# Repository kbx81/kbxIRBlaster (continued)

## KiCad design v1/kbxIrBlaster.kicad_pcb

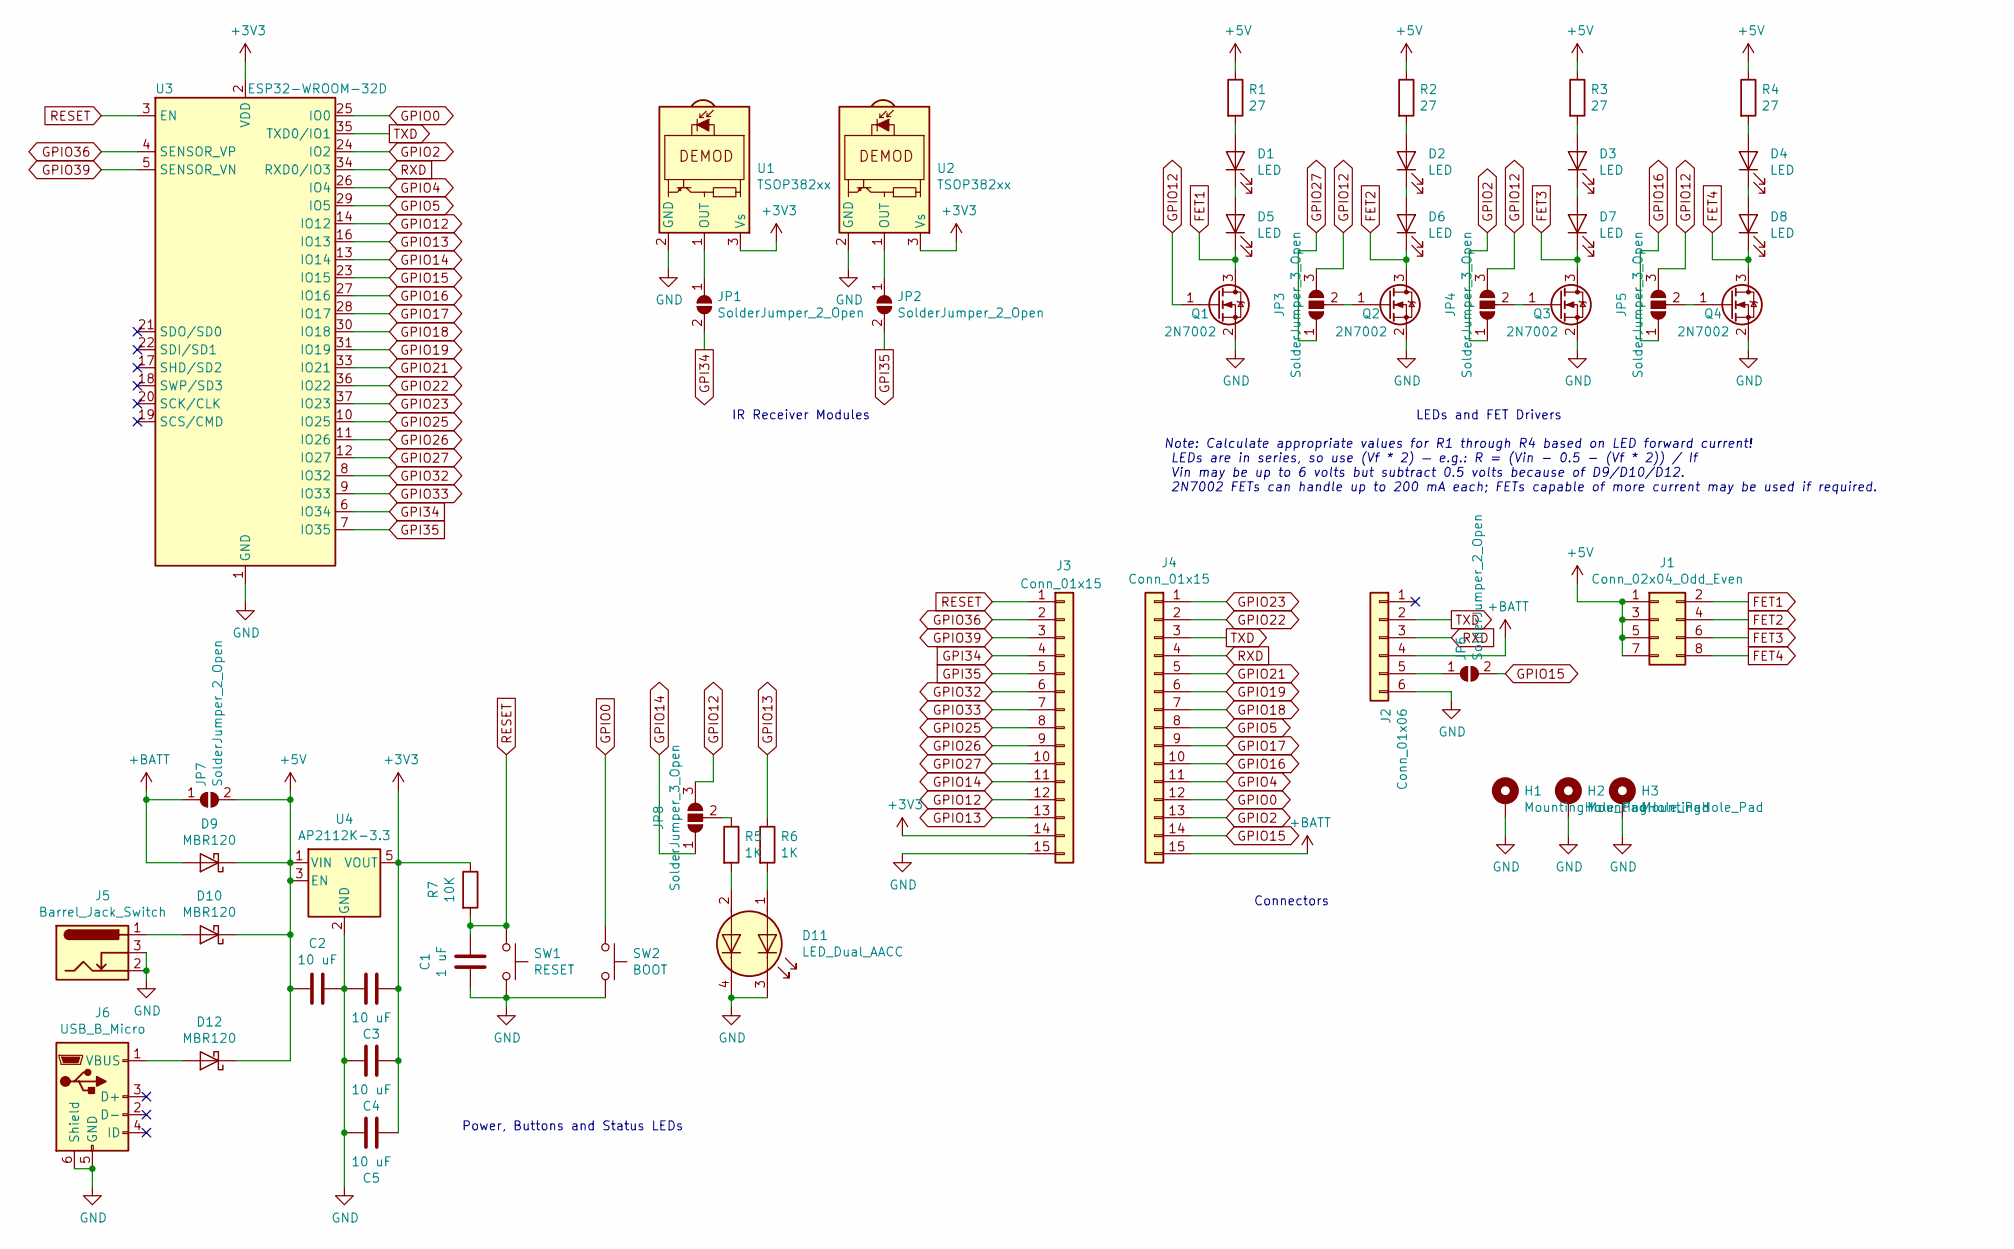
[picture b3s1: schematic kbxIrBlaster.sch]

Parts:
C1: 1 uF; C_0805_2012Metric_Pad1.15x1.40mm_HandSolder; MPN1 C0805C105K4RACTU
C2, C3, C4, C5: 10 uF; C_0805_2012Metric_Pad1.15x1.40mm_HandSolder; MPN1 GRM21BC81C106ME15L
D1, D2, D3, D4, D5, D6, D7, D8: LED; LED_D5.0mm; MPN1 LTE-4206
D9, D10, D12: MBR120; D_SOD-123F; MPN1 MBR120VLSFT1G
D11: LED_Dual_AACC; LED_Cree-PLCC4_3.2x2.8mm_CCW; MPN1 APB3025ESGC-F01
H1, H2, H3: MountingHole_Pad; MountingHole_2.5mm_Pad_Via
J1: Conn_02x04_Odd_Even; PinHeader_2x04_P2.54mm_Vertical
J2: Conn_01x06; PinHeader_1x06_P2.54mm_Vertical
J3, J4: Conn_01x15; PinHeader_1x15_P2.54mm_Vertical
J5: Barrel_Jack_Switch; BarrelJack_Horizontal; MPN1 163-179PH-EX
J6: USB_B_Micro; USB_Micro-B_Molex-105017-0001; MPN1 105017-0001
JP1, JP2, JP6, JP7: SolderJumper_2_Open; SolderJumper-2_P1.3mm_Open_RoundedPad1.0x1.5mm
JP3, JP4, JP5, JP8: SolderJumper_3_Open; SolderJumper-3_P1.3mm_Open_RoundedPad1.0x1.5mm
Q1, Q2, Q3, Q4: 2N7002; SOT-23; MPN1 2N7002-7-F
R1, R2, R3, R4: 27; R_0805_2012Metric_Pad1.15x1.40mm_HandSolder; MPN1 RC0805FR-0727RL
R5, R6: 1K; R_0805_2012Metric_Pad1.15x1.40mm_HandSolder; MPN1 RC0805FR-071KL
R7: 10K; R_0805_2012Metric_Pad1.15x1.40mm_HandSolder; MPN1 RC0805FR-0710KL
SW1: RESET; SW_Push_1P1T_NO_CK_KMR2; MPN1 KMR221GLFS
SW2: BOOT; SW_Push_1P1T_NO_CK_KMR2; MPN1 KMR221GLFS
U1: TSOP382xx; Vishay_MINICAST-3Pin; MPN1 TSOP38238
U2: TSOP382xx; Vishay_MINICAST-3Pin; MPN1 TSOP38256
U3: ESP32-WROOM-32D; ESP32-WROOM-32; MPN1 ESP32-WROOM-32D
U4: AP2112K-3.3; SOT-23-5; MPN1 AP2112K-3.3TRG1

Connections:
+3V3: C3.2, C4.2, C5.2, J3.14, R7.1, U1.3 (Vs), U2.3 (Vs), U3.2 (VDD), U4.5 (VOUT)
+5V: C2.2, D9.1 (K), D10.1 (K), D12.1 (K), J1.1, J1.3, J1.5, J1.7, JP7.2 (B), R1.1, R2.1, R3.1, R4.1, U4.1 (VIN), U4.3 (EN)
+BATT: D9.2 (A), J2.4, J4.15, JP7.1 (A)
FET1: D5.1 (K), J1.2, Q1.3 (D)
FET2: D6.1 (K), J1.4, Q2.3 (D)
FET3: D7.1 (K), J1.6, Q3.3 (D)
FET4: D8.1 (K), J1.8, Q4.3 (D)
GND: C1.2, C2.1, C3.1, C4.1, C5.1, D11.3 (K1), D11.4 (K2), H1.1, H2.1, H3.1, J2.6, J3.15, J5.2, J5.3, J6.5 (GND), J6.6 (Shield), Q1.2 (S), Q2.2 (S), Q3.2 (S), Q4.2 (S), SW1.2, SW2.2, U1.2 (GND), U2.2 (GND), U3.1 (GND), U3.15 (GND), U3.38 (GND), U3.39 (GND), U4.2 (GND)
GPI34: J3.4, JP1.2 (B), U3.6 (IO34)
GPI35: J3.5, JP2.2 (B), U3.7 (IO35)
GPIO0: J4.12, SW2.1, U3.25 (IO0)
GPIO2: J4.13, JP4.1 (A), U3.24 (IO2)
GPIO4: J4.11, U3.26 (IO4)
GPIO5: J4.8, U3.29 (IO5)
GPIO12: J3.12, JP3.3 (B), JP4.3 (B), JP5.3 (B), JP8.3 (B), Q1.1 (G), U3.14 (IO12)
GPIO13: J3.13, R6.1, U3.16 (IO13)
GPIO14: J3.11, JP8.1 (A), U3.13 (IO14)
GPIO15: J4.14, JP6.2 (B), U3.23 (IO15)
GPIO16: J4.10, JP5.1 (A), U3.27 (IO16)
GPIO17: J4.9, U3.28 (IO17)
GPIO18: J4.7, U3.30 (IO18)
GPIO19: J4.6, U3.31 (IO19)
GPIO21: J4.5, U3.33 (IO21)
GPIO22: J4.2, U3.36 (IO22)
GPIO23: J4.1, U3.37 (IO23)
GPIO25: J3.8, U3.10 (IO25)
GPIO26: J3.9, U3.11 (IO26)
GPIO27: J3.10, JP3.1 (A), U3.12 (IO27)
GPIO32: J3.6, U3.8 (IO32)
GPIO33: J3.7, U3.9 (IO33)
GPIO36: J3.2, U3.4 (SENSOR_VP)
GPIO39: J3.3, U3.5 (SENSOR_VN)
unnamed: D1.1 (K), D5.2 (A)
unnamed: D1.2 (A), R1.2
unnamed: D2.1 (K), D6.2 (A)
unnamed: D2.2 (A), R2.2
unnamed: D3.1 (K), D7.2 (A)
unnamed: D3.2 (A), R3.2
unnamed: D4.1 (K), D8.2 (A)
unnamed: D4.2 (A), R4.2
unnamed: D10.2 (A), J5.1
unnamed: D11.1 (A1), R6.2
unnamed: D11.2 (A2), R5.2
unnamed: D12.2 (A), J6.1 (VBUS)
unnamed: J2.5, JP6.1 (A)
unnamed: JP1.1 (A), U1.1 (OUT)
unnamed: JP2.1 (A), U2.1 (OUT)
unnamed: JP3.2 (C), Q2.1 (G)
unnamed: JP4.2 (C), Q3.1 (G)
unnamed: JP5.2 (C), Q4.1 (G)
unnamed: JP8.2 (C), R5.1
RESET: C1.1, J3.1, R7.2, SW1.1, U3.3 (EN)
RXD: J2.3, J4.4, U3.34 (RXD0/IO3)
TXD: J2.2, J4.3, U3.35 (TXD0/IO1)

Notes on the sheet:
LEDs and FET Drivers
IR Receiver Modules
Power, Buttons and Status LEDs
Connectors
Note: Calculate appropriate values for R1 through R4 based on LED forward current! LEDs are in series, so use (Vf * 2) — e.g.: R = (Vin - 0.5 - (Vf * 2)) / If Vin may be up to 6 volts but subtract 0.5 volts because of D9/D10/D12. 2N7002 FETs can handle up to 200 mA each; FETs capable of more curren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

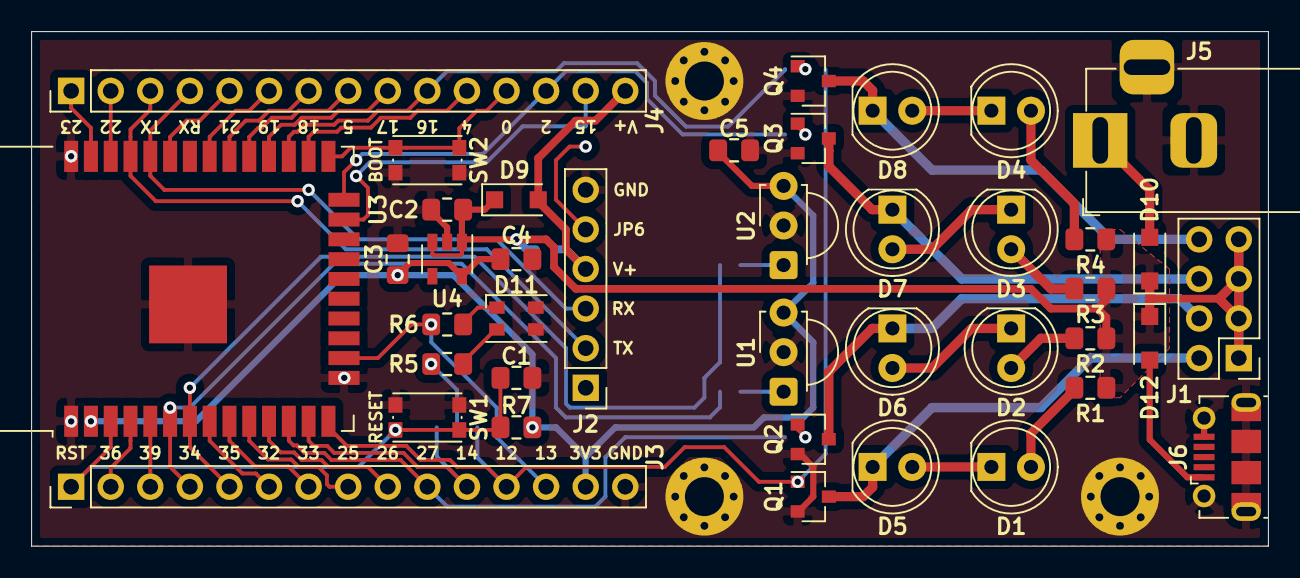
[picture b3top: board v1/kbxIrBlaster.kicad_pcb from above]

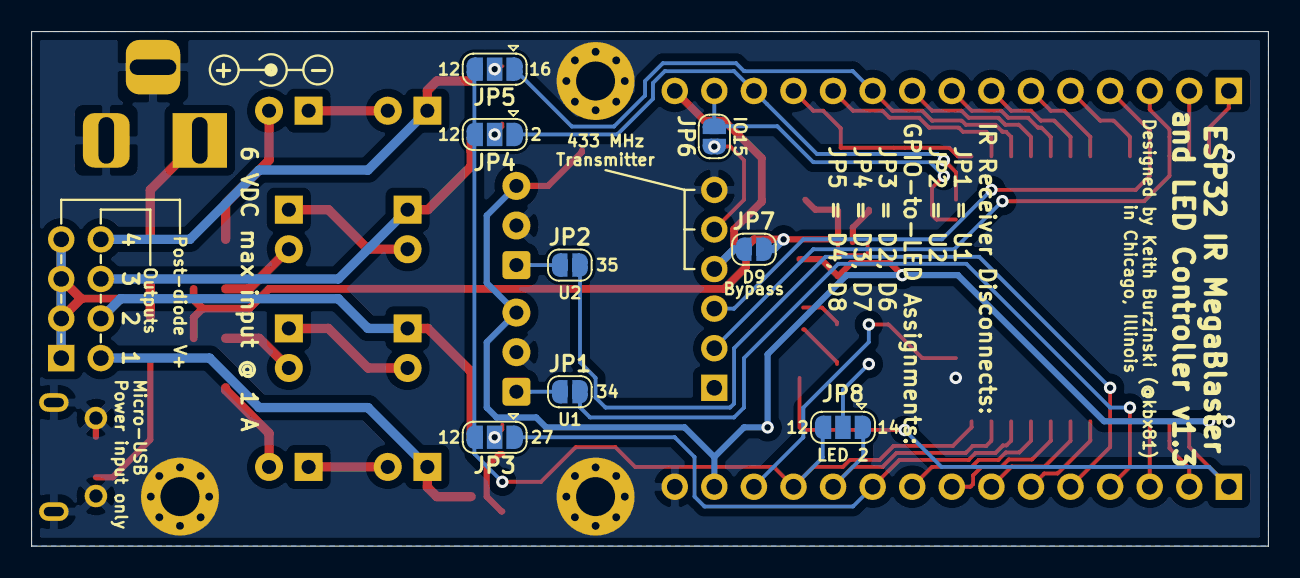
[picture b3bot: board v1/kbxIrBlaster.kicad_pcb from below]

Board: 2 copper layers, 79.4 x 33.0 mm, 51 parts (8 on the bottom side), 54 nets.

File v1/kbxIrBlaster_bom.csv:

Component,Quantity Per PCB,References,Value,MPN1,MPN2,Footprint,Population
1,1,C1,1 uF,C0805C105K4RACTU,-,C_0805_2012Metric_Pad1.15x1.40mm_HandSolder,
2,4,C2 C3 C4 C5,10 uF,GRM21BC81C106ME15L,-,C_0805_2012Metric_Pad1.15x1.40mm_HandSolder,
3,8,D1 D2 D3 D4 D5 D6 D7 D8,LED,LTE-4206,-,LED_D5.0mm,
4,1,D11,LED_Dual_AACC,APB3025ESGC-F01,-,LED_Cree-PLCC4_3.2x2.8mm_CCW,
5,3,D9 D10 D12,MBR120,MBR120VLSFT1G,-,D_SOD-123F,
6,1,J5,Barrel_Jack_Switch,163-179PH-EX,-,BarrelJack_Horizontal,
7,1,J6,USB_B_Micro,105017-0001,-,USB_Micro-B_Molex-105017-0001,
8,4,Q1 Q2 Q3 Q4,2N7002,2N7002-7-F,-,SOT-23,
9,4,R1 R2 R3 R4,27,RC0805FR-0727RL,-,R_0805_2012Metric_Pad1.15x1.40mm_HandSolder,
10,2,R5 R6,1K,RC0805FR-071KL,-,R_0805_2012Metric_Pad1.15x1.40mm_HandSolder,
11,1,R7,10K,RC0805FR-0710KL,-,R_0805_2012Metric_Pad1.15x1.40mm_HandSolder,
12,1,SW2,BOOT,KMR221GLFS,-,SW_Push_1P1T_NO_CK_KMR2,
13,1,SW1,RESET,KMR221GLFS,-,SW_Push_1P1T_NO_CK_KMR2,
14,1,U4,AP2112K-3.3,AP2112K-3.3TRG1,-,SOT-23-5,
15,1,U3,ESP32-WROOM-32D,ESP32-WROOM-32D,-,ESP32-WROOM-32,
16,2,U1 U2,TSOP382xx,TSOP38238 TSOP38256,-,Vishay_MINICAST-3Pin,

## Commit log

2020-04-03 BoM fix
2020-04-03 Added images
2020-04-03 Fixed filename
2020-04-09 PCB refinements
2021-06-14 Add v2 and other updates
2021-06-14 Add image gallery
2021-06-14 Copy tweaks
2021-11-10 Update README.md
    https://forum.kicad.info/t/warning-avoid-all-links-to-kicad-pcb-org-use-kicad-org/31521
2022-04-15 v3 initial commit
2024-12-29 Update with v3
2024-12-29 Rework image gallery
2024-12-29 Copy fix
2024-12-29 One more...
2025-03-04 Add v4
